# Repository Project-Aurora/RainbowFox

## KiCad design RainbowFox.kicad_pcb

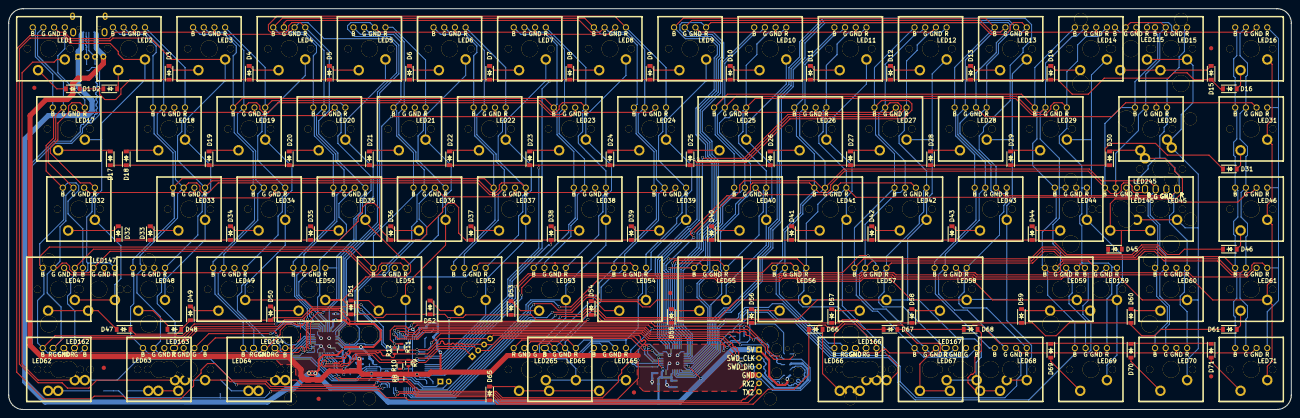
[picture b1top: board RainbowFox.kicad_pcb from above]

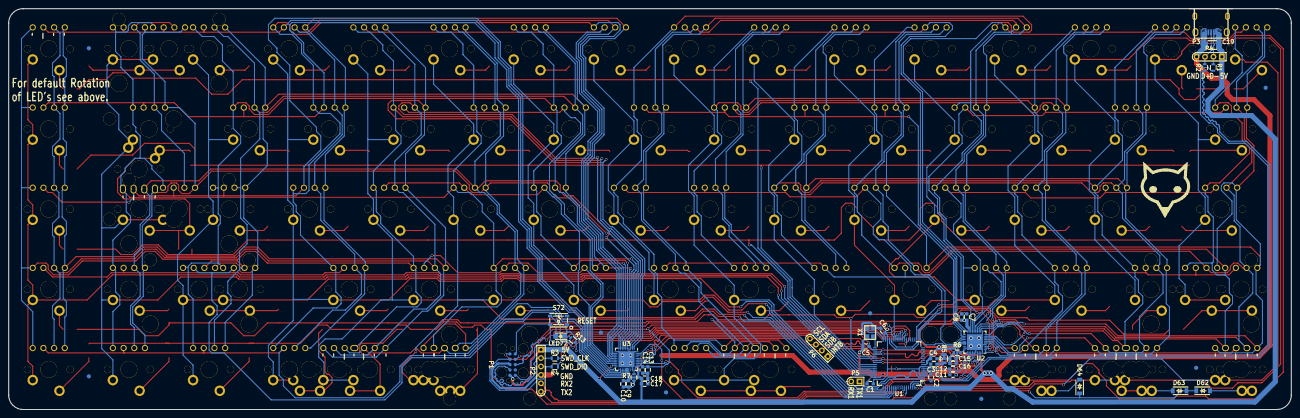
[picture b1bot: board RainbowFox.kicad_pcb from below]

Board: 2 copper layers, 304.8 x 95.3 mm, 299 parts (42 on the bottom side), 166 nets.

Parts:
C1, C2, C5, C6, C8, C10, C12, C14, C16, C17: 0.1uF; C_0603
C3, C4: 2.2uF; C_0603
C7, C9, C11, C13, C15, C18: 1uF; C_0603
C19: 100uF; C_1206
D1, D2, D3, D4, D5, D6, D7, D8, D9, D10, D11, D12, D13, D14, D15, D16, D17, D18, D19, D20, D21, D22, D23, D24, D25, D26, D27, D28, D29, D30, D31, D32, D33, D34, D35, D36, D37, D38, D39, D40, D41, D42, D43, D44, D45, D46, D47, D48, D49, D50, D51, D52, D53, D54, D55, D56, D57, D58, D59, D60, D61, D62, D63, D64, D65, D66, D67, D68, D69, D70, D71: DIODE; SOD-123
LED1, LED2, LED3, LED4, LED5, LED6, LED7, LED8, LED9, LED10, LED11, LED12, LED13, LED14, LED15, LED16, LED17, LED18, LED19, LED20, LED21, LED22, LED23, LED24, LED25, LED26, LED27, LED28, LED29, LED30, LED31, LED32, LED33, LED34, LED35, LED36, LED37, LED38, LED39, LED40, LED41, LED42, LED43, LED44, LED45, LED46, LED47, LED48, LED49, LED50, LED51, LED52, LED53, LED54, LED55, LED56, LED57, LED58, LED59, LED60, LED61, LED62, LED63, LED64, LED65, LED66, LED67, LED68, LED69, LED70, LED71, LED115, LED145, LED147, LED159, LED165: Led_RGB_CA; RGB
LED72: LED; LED_0805
LED162, LED163, LED164, LED166, LED167, LED245, LED265: Led_RGB_CA; RGB-reverse
P1: FLASH_HDR; JLINK_NEEDLE
P2: CONN_01X06; Conn-6
P3: USB_OTG; Micro-USB_629105150521
P4, P6: CONN_01X04; Conn-4
P5: CONN_01X02; Conn-2
R1, R2: 33; R_0603
R3, R4: 100; R_0603
R5: 5M; R_0805
R6, R7: 20k; R_0603
R8, R9, R10: 100k; R_0603
R11, R12: 4.7k; R_0603
R13: 1k; R_0603
S1, S2, S3, S4, S5, S6, S7, S8, S9, S10, S11, S12, S13, S14, S15, S16, S17, S18, S19, S20, S21, S22, S23, S24, S25, S26, S27, S28, S29, S30, S31, S32, S33, S34, S35, S36, S37, S38, S39, S40, S41, S42, S43, S44, S45, S46, S47, S48, S49, S50, S51, S52, S53, S54, S55, S56, S57, S58, S59, S60, S61, S62, S63, S64, S65, S66, S67, S68, S69, S70, S71: SW; MX1A
S72: TAC_SWITCH; PTS810
S115, S145, S147, S159, S162, S163, S164, S165, S166, S167, S168, S245, S263, S265, S266: SW; MX1A-Borderless
STAB1, STAB2, STAB3, STAB4, STAB5, STAB6, STAB7, STAB8, STAB9, STAB10, STAB11, STAB12, STAB13, STAB14, STAB15: STAB
U1: MK20DX256VLH7; LQFP-64_10x10mm_Pitch0.5mm
U2, U3: IS31FL3737; UQFN-40-1EP_5x5mm_Pitch0.4mm
X1: CRYSTAL_SMD; crystal_FA238-TSX3225

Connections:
+3V3: C1.1, C2.1, C3.1, C6.1, C11.1, C12.1, C13.1, C14.1, P1.1, R10.2, R11.2, R12.2, U1.3, U1.7, U1.21, U1.30, U1.48, U2.32, U3.32
+5V: C4.1, C7.1, C8.1, C9.1, C10.1, C15.1, C16.1, C17.1, C18.1, C19.1, P1.5, P2.1, P3.1, P4.1, U1.8, U2.19, U2.26, U2.31, U3.19, U3.26, U3.31, U3.36
/ledmatrix/IICRST: R8.1, U2.39, U3.39
/ledmatrix/INTB: P6.1, R10.1, U1.40, U2.37
/ledmatrix/LED-A/CS1: LED62.1, LED63.1, LED64.1, LED65.1, LED162.1, LED163.1, LED164.1, LED165.1, LED265.1, U2.15
/ledmatrix/LED-A/CS2: LED47.1, LED48.1, LED49.1, LED50.1, LED147.1, U2.16
/ledmatrix/LED-A/CS3: LED32.1, LED33.1, LED34.1, LED35.1, U2.17
/ledmatrix/LED-A/CS4: LED17.1, LED18.1, LED19.1, LED20.1, U2.18
/ledmatrix/LED-A/CS5: LED1.1, LED2.1, LED3.1, LED4.1, U2.20
/ledmatrix/LED-A/CS6: LED5.1, LED6.1, LED7.1, LED8.1, U2.21
/ledmatrix/LED-A/CS7: LED21.1, LED22.1, LED23.1, LED24.1, U2.22
/ledmatrix/LED-A/CS8: LED36.1, LED37.1, LED38.1, LED39.1, U2.23
/ledmatrix/LED-A/CS9: LED51.1, LED52.1, LED53.1, LED54.1, U2.24
/ledmatrix/LED-A/SW1: LED4.3, LED8.3, LED20.3, LED24.3, LED35.3, LED39.3, LED50.3, LED54.3, LED65.3, LED165.3, LED265.3, U2.1
/ledmatrix/LED-A/SW2: LED4.2, LED8.2, LED20.2, LED24.2, LED35.2, LED39.2, LED50.2, LED54.2, LED65.2, LED165.2, LED265.2, U2.2
/ledmatrix/LED-A/SW3: LED4.4, LED8.4, LED20.4, LED24.4, LED35.4, LED39.4, LED50.4, LED54.4, LED65.4, LED165.4, LED265.4, U2.3
/ledmatrix/LED-A/SW4: LED3.3, LED7.3, LED19.3, LED23.3, LED34.3, LED38.3, LED49.3, LED53.3, LED64.3, LED164.3, U2.5
/ledmatrix/LED-A/SW5: LED3.2, LED7.2, LED19.2, LED23.2, LED34.2, LED38.2, LED49.2, LED53.2, LED64.2, LED164.4, U2.6
/ledmatrix/LED-A/SW6: LED3.4, LED7.4, LED19.4, LED23.4, LED34.4, LED38.4, LED49.4, LED53.4, LED64.4, LED164.2, U2.7
/ledmatrix/LED-A/SW7: LED2.3, LED6.3, LED18.3, LED22.3, LED33.3, LED37.3, LED48.3, LED52.3, LED63.3, LED163.3, U2.8
/ledmatrix/LED-A/SW8: LED2.2, LED6.2, LED18.2, LED22.2, LED33.2, LED37.2, LED48.2, LED52.2, LED63.2, LED163.2, U2.9
/ledmatrix/LED-A/SW9: LED2.4, LED6.4, LED18.4, LED22.4, LED33.4, LED37.4, LED48.4, LED52.4, LED63.4, LED163.4, U2.10
/ledmatrix/LED-A/SW10: LED1.3, LED5.3, LED17.3, LED21.3, LED32.3, LED36.3, LED47.3, LED51.3, LED62.3, LED147.3, LED162.3, U2.12
/ledmatrix/LED-A/SW11: LED1.2, LED5.2, LED17.2, LED21.2, LED32.2, LED36.2, LED47.2, LED51.2, LED62.2, LED147.2, LED162.4, U2.13
/ledmatrix/LED-A/SW12: LED1.4, LED5.4, LED17.4, LED21.4, LED32.4, LED36.4, LED47.4, LED51.4, LED62.4, LED147.4, LED162.2, U2.14
/ledmatrix/LED-B/CS1: LED9.1, LED10.1, LED11.1, LED12.1, U3.15
/ledmatrix/LED-B/CS2: LED25.1, LED26.1, LED27.1, U3.16
/ledmatrix/LED-B/CS3: LED55.1, LED56.1, LED57.1, U3.17
/ledmatrix/LED-B/CS4: LED40.1, LED41.1, LED42.1, U3.18
/ledmatrix/LED-B/CS5: LED43.1, LED44.1, LED45.1, LED46.1, LED145.1, LED245.1, U3.20
/ledmatrix/LED-B/CS6: LED13.1, LED14.1, LED15.1, LED16.1, LED115.1, U3.21
/ledmatrix/LED-B/CS7: LED28.1, LED29.1, LED30.1, LED31.1, U3.22
/ledmatrix/LED-B/CS8: LED66.1, LED67.1, LED166.1, LED167.1, U3.23
/ledmatrix/LED-B/CS9: LED68.1, LED69.1, LED70.1, LED71.1, U3.24
/ledmatrix/LED-B/CS10: LED58.1, LED59.1, LED60.1, LED61.1, LED159.1, U3.25
/ledmatrix/LED-B/SW1: LED12.3, LED16.3, LED27.3, LED31.3, LED42.3, LED46.3, LED57.3, LED61.3, LED67.3, LED71.3, LED167.3, U3.1
/ledmatrix/LED-B/SW2: LED12.2, LED16.2, LED27.2, LED31.2, LED42.2, LED46.2, LED57.2, LED61.2, LED67.2, LED71.2, LED167.2, U3.2
/ledmatrix/LED-B/SW3: LED12.4, LED16.4, LED27.4, LED31.4, LED42.4, LED46.4, LED57.4, LED61.4, LED67.4, LED71.4, LED167.4, U3.3
/ledmatrix/LED-B/SW4: LED11.3, LED15.3, LED26.3, LED30.3, LED41.3, LED45.3, LED56.3, LED60.3, LED66.3, LED70.3, LED115.3, LED145.3, LED166.3, LED245.3, U3.5
/ledmatrix/LED-B/SW5: LED11.2, LED15.2, LED26.2, LED30.2, LED41.2, LED45.2, LED56.2, LED60.2, LED66.2, LED70.2, LED115.2, LED145.2, LED166.4, LED245.2, U3.6
/ledmatrix/LED-B/SW6: LED11.4, LED15.4, LED26.4, LED30.4, LED41.4, LED45.4, LED56.4, LED60.4, LED66.4, LED70.4, LED115.4, LED145.4, LED166.2, LED245.4, U3.7
/ledmatrix/LED-B/SW7: LED10.3, LED14.3, LED25.3, LED29.3, LED40.3, LED44.3, LED55.3, LED59.3, LED69.3, LED159.3, U3.8
/ledmatrix/LED-B/SW8: LED10.2, LED14.2, LED25.2, LED29.2, LED40.2, LED44.2, LED55.2, LED59.2, LED69.2, LED159.2, U3.9
/ledmatrix/LED-B/SW9: LED10.4, LED14.4, LED25.4, LED29.4, LED40.4, LED44.4, LED55.4, LED59.4, LED69.4, LED159.4, U3.10
/ledmatrix/LED-B/SW10: LED9.3, LED13.3, LED28.3, LED43.3, LED58.3, LED68.3, U3.12
/ledmatrix/LED-B/SW11: LED9.2, LED13.2, LED28.2, LED43.2, LED58.2, LED68.2, U3.13
/ledmatrix/LED-B/SW12: LED9.4, LED13.4, LED28.4, LED43.4, LED58.4, LED68.4, U3.14
/ledmatrix/SCL: P6.4, R11.1, U1.35, U2.35, U3.35
/ledmatrix/SDA: P6.3, R12.1, U1.36, U2.34, U3.34
/ledmatrix/SDB: P6.2, R9.1, U1.39, U2.38, U3.38
/ledmatrix/Sync: U2.33, U3.33
/mcu/D+: R2.1, U1.5
/mcu/D-: R1.1, U1.6
/mcu/MCU_RESET: C5.1, P1.10, S72.2, U1.34
/mcu/PTA4: S6.1, S21.1, S36.1, S51.1, U1.26
/mcu/PTA5: LED72.2, P1.9, U1.27
/mcu/PTA12: S5.1, S20.1, S35.1, S50.1, U1.28
/mcu/PTA13: S4.1, S19.1, S34.1, S49.1, U1.29
/mcu/PTB2: D47.1, D48.1, D49.1, D50.1, D51.1, D52.1, D53.1, D54.1, D55.1, D56.1, D57.1, D58.1, D59.1, D60.1, D61.1, U1.37
/mcu/PTB3: S7.1, S22.1, S37.1, S52.1, U1.38
/mcu/PTB18: D17.1, D18.1, D19.1, D20.1, D21.1, D22.1, D23.1, D24.1, D25.1, D26.1, D27.1, D28.1, D29.1, D30.1, D31.1, U1.41
/mcu/PTB19: D1.1, D2.1, D3.1, D4.1, D5.1, D6.1, D7.1, D8.1, D9.1, D10.1, D11.1, D12.1, D13.1, D14.1, D15.1, D16.1, U1.42
/mcu/PTC0: D32.1, D33.1, D34.1, D35.1, D36.1, D37.1, D38.1, D39.1, D40.1, D41.1, D42.1, D43.1, D44.1, D45.1, D46.1, U1.43
/mcu/PTC1: S16.1, S31.1, S46.1, S61.1, S71.1, U1.44
/mcu/PTC2: S15.1, S30.1, S45.1, S60.1, S70.1, S115.1, S145.1, S245.2, U1.45
/mcu/PTC3: S14.1, S29.1, S44.1, S59.1, S69.1, S159.1, U1.46
/mcu/PTC4: S8.1, S23.1, S38.1, S53.1, S65.1, S165.1, S265.1, U1.49
/mcu/PTC5: S13.1, S28.1, S43.1, S58.1, S68.1, S168.1, U1.50
/mcu/PTC6: S9.1, S24.1, S39.1, S54.1, U1.51
/mcu/PTC7: S10.1, S25.1, S40.1, S55.1, U1.52
/mcu/PTC8: S11.1, S26.1, S41.1, S56.1, S66.1, S166.1, S266.1, U1.53
/mcu/PTC9: S12.1, S27.1, S42.1, S57.1, S67.1, S167.1, U1.54
/mcu/PTC10: D62.1, D63.1, D64.1, D65.1, D66.1, D67.1, D68.1, D69.1, D70.1, D71.1, U1.55
/mcu/PTD5: S3.1, S18.1, S33.1, S48.1, S64.1, S164.1, U1.62
/mcu/PTD6: S2.1, S17.1, S32.1, S47.1, S63.1, S147.1, S163.1, S263.1, U1.63
/mcu/PTD7: S1.1, S62.1, S162.1, U1.64
/mcu/RX0: P1.8, U1.23
/mcu/RX1: P5.2, U1.1
/mcu/RX2: P2.5, U1.59
/mcu/SWD_CLK: P1.4, P2.2, R3.2
/mcu/SWD_DIO: P1.2, P2.3, R4.2
/mcu/TX0: P1.6, U1.24
/mcu/TX1: P5.1, U1.2
/mcu/TX2: P2.6, U1.60
/mcu/USB_D+: P3.3, P4.3, R2.2
/mcu/USB_D-: P3.2, P4.2, R1.2
GND: C1.2, C2.2, C4.2, C5.2, C6.2, C7.2, C8.2, C9.2, C10.2, C11.2, C12.2, C13.2, C14.2, C15.2, C16.2, C17.2, C18.2, C19.2, P1.3, P2.4, P3.5, P4.4, R5.2, R6.1, R7.1, R8.2, R9.2, R13.2, S72.4, U1.4, U1.31, U1.47, U2.4, U2.11, U2.29, U2.36, U2.40, U2.41, U3.4, U3.11, U3.29, U3.40, U3.41, X1.3
unnamed: C3.2, R5.1
unnamed: D1.2, S1.2
unnamed: D2.2, S2.2
unnamed: D3.2, S3.2
unnamed: D4.2, S4.2
unnamed: D5.2, S5.2
unnamed: D6.2, S6.2
unnamed: D7.2, S7.2
unnamed: D8.2, S8.2
unnamed: D9.2, S9.2
unnamed: D10.2, S10.2
unnamed: D11.2, S11.2
unnamed: D12.2, S12.2
unnamed: D13.2, S13.2
unnamed: D14.2, S14.2
unnamed: D15.2, S15.2, S115.2
unnamed: D16.2, S16.2
unnamed: D17.2, S17.2
unnamed: D18.2, S18.2
unnamed: D19.2, S19.2
unnamed: D20.2, S20.2
unnamed: D21.2, S21.2
unnamed: D22.2, S22.2
unnamed: D23.2, S23.2
unnamed: D24.2, S24.2
unnamed: D25.2, S25.2
unnamed: D26.2, S26.2
unnamed: D27.2, S27.2
unnamed: D28.2, S28.2
unnamed: D29.2, S29.2
unnamed: D30.2, S30.2
unnamed: D31.2, S31.2
unnamed: D32.2, S32.2
unnamed: D33.2, S33.2
unnamed: D34.2, S34.2
unnamed: D35.2, S35.2
unnamed: D36.2, S36.2
unnamed: D37.2, S37.2
unnamed: D38.2, S38.2
unnamed: D39.2, S39.2
unnamed: D40.2, S40.2
unnamed: D41.2, S41.2
unnamed: D42.2, S42.2
unnamed: D43.2, S43.2
unnamed: D44.2, S44.2
unnamed: D45.2, S45.2, S145.2, S245.1
unnamed: D46.2, S46.2
unnamed: D47.2, S47.2, S147.2
unnamed: D48.2, S48.2
unnamed: D49.2, S49.2
unnamed: D50.2, S50.2
unnamed: D51.2, S51.2
unnamed: D52.2, S52.2
unnamed: D53.2, S53.2
unnamed: D54.2, S54.2
unnamed: D55.2, S55.2
unnamed: D56.2, S56.2
unnamed: D57.2, S57.2
unnamed: D58.2, S58.2
unnamed: D59.2, S59.2, S159.2
unnamed: D60.2, S60.2
unnamed: D61.2, S61.2
unnamed: D62.2, S62.2, S162.2
unnamed: D63.2, S63.2, S163.2, S263.2
unnamed: D64.2, S64.2, S164.2
unnamed: D65.2, S65.2, S165.2, S265.2
unnamed: D66.2, S66.2, S166.2, S266.2
unnamed: D67.2, S67.2, S167.2
unnamed: D68.2, S68.2, S168.2
unnamed: D69.2, S69.2
unnamed: D70.2, S70.2
unnamed: D71.2, S71.2
unnamed: LED72.1, R13.1
unnamed: R3.1, U1.22
unnamed: R4.1, U1.25
unnamed: R6.2, U2.30
unnamed: R7.2, U3.30
unnamed: U1.32, X1.1
unnamed: U1.33, X1.2

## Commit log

2016-06-26 :neckbeard: Added .gitattributes & .gitignore files
2016-06-26 Fixed Orientation of Keyboard-Diodes
2016-07-10 Did some cleanup
2016-08-14 Switched to different Debug Ports
2016-11-30 Addressed the Points raised in Issue #2
    Added Resistor to ground for firmware-LED
    Connect VBAT to 3.3V
2016-12-01 Properly replaced the Footprint of the Reset Switch
2016-12-02 Replaced GND with CA in LED Silkscreen
